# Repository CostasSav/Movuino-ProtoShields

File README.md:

# Movuino-ProtoShields
Development of shields for prototyping using the Movuino

# MovuinoESP8266.pretty folder
Library folder that contains multiple useful part footprints linked to the ESP8266 but also the ESP32

# MovuinoProtoShield_v1.0 folder
Folder containing the first version of the Movuino ProtoShield. The main file is the MovuinoShieldPrototyping.kicad_pro, 
which is a Kicad project containing the schematics and the pcb of the shield. There is also the GerberFiles folder which 
contains all the drilling/gerber files to manifacture the shield.

# MovuinoProtoShield_v2.0 folder
Folder containing the second version of the Movuino ProtoShield, but also multiple other alternative designs that have not been fully developed yet. 
The main file is the MovuinoProtoShield_v2.0.kicad_pro, which is a Kicad project containing the schematics and the pcb of the shield.
In the file MovuinoProtoShield_versions_multiples.kicad_pro, we have the alternative designs mentionned previously.
There is also the GerberFiles folder which contains all the drilling/gerber files to manifacture the shield.

# part-lib folder
Library folder containing important part footprints used in the development of shields for the Movuino.
Most notably, we have the shield connector (DF12_3.0_-36DP-0.5V_86_ folder)

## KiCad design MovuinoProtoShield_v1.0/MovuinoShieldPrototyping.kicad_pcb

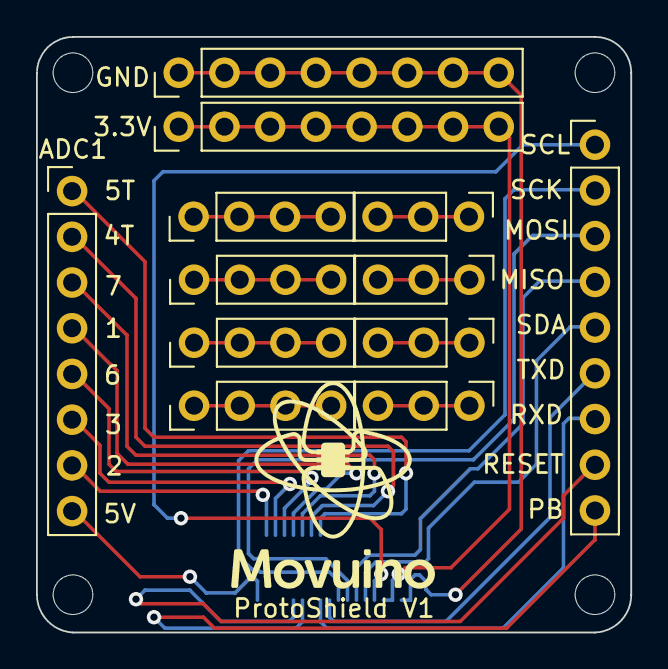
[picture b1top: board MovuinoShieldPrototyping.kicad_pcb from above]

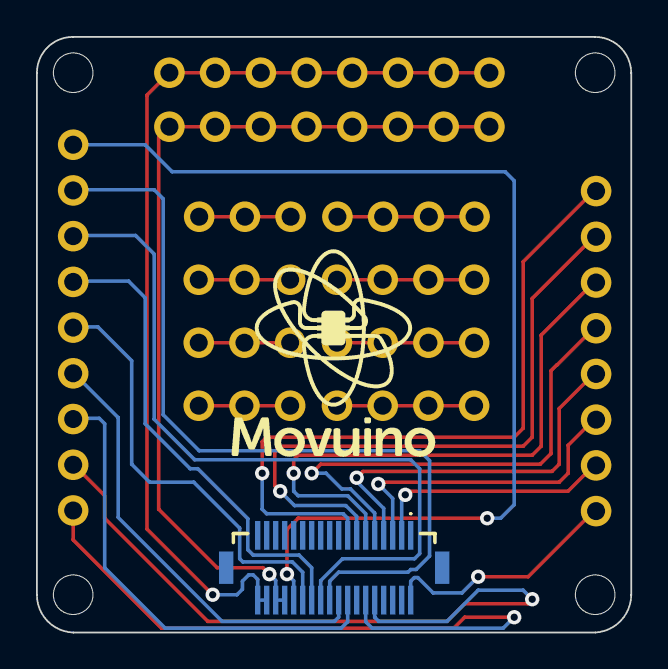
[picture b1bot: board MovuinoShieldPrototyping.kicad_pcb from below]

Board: 2 copper layers, 33.0 x 33.1 mm, 4 parts (2 on the bottom side), 10 nets.

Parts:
7: PinHeader_1x08_P2.54mm_Vertical
J6: DF12_3.0_-36DP_0.5V_86_; DF123036DP05V86
U$8, U$8#2: LOGO_MOVUINOBOTTOM_11MM; LOGO_MOVUINO_BMP_11MM-BOTTOM

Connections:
+3V3: J6.30, J6.32
+5V: 7.8, J6.2
ADC1.1: 7.4, J6.9
ADC1.2: 7.7, J6.3
ADC1.3: 7.6, J6.5
ADC1.4T: 7.2, J6.13
ADC1.5T: 7.1, J6.15
ADC1.6: 7.5, J6.7
ADC1.7: 7.3, J6.11
GND: J6.34, J6.36
